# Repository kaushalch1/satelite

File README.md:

# Live ysws satelite

## satelite Telemetry and Mission Control System

**Live-X01** is a miniature CubeSat-inspired flight computer and telemetry system built around an ESP32. The project combines real-time sensor monitoring, telemetry logging, system diagnostics, and a dedicated mission-control interface.

The design is intended to look and behave like a small satellite flight computer while remaining practical to prototype and simulate.

---

## Project Overview

Live satelite monitors the satellite's internal systems and displays important telemetry through an OLED interface.

The system can monitor:

- Temperature
- Acceleration and orientation
- Battery voltage
- Storage status
- System status
- Mission status
- Twitch Live stream status

Telemetry can also be stored on a microSD card for later analysis.

---

## Main Features

### Flight Computer

The ESP32 acts as the main flight computer responsible for:

- Sensor communication
- Telemetry processing
- Display control
- Data logging
- Button input
- Status indication
- Mission-state management

### Telemetry Display

The OLED provides a compact mission dashboard.

Example:

```text
CUBESAT-X01
----------------
HACK CLUB LIVE
STREAM: ONLINE

TEMP: 27.4 C
BAT: 82%
IMU: ONLINE
SD: ONLINE

MISSION: ACTIVE

```
##pcb:

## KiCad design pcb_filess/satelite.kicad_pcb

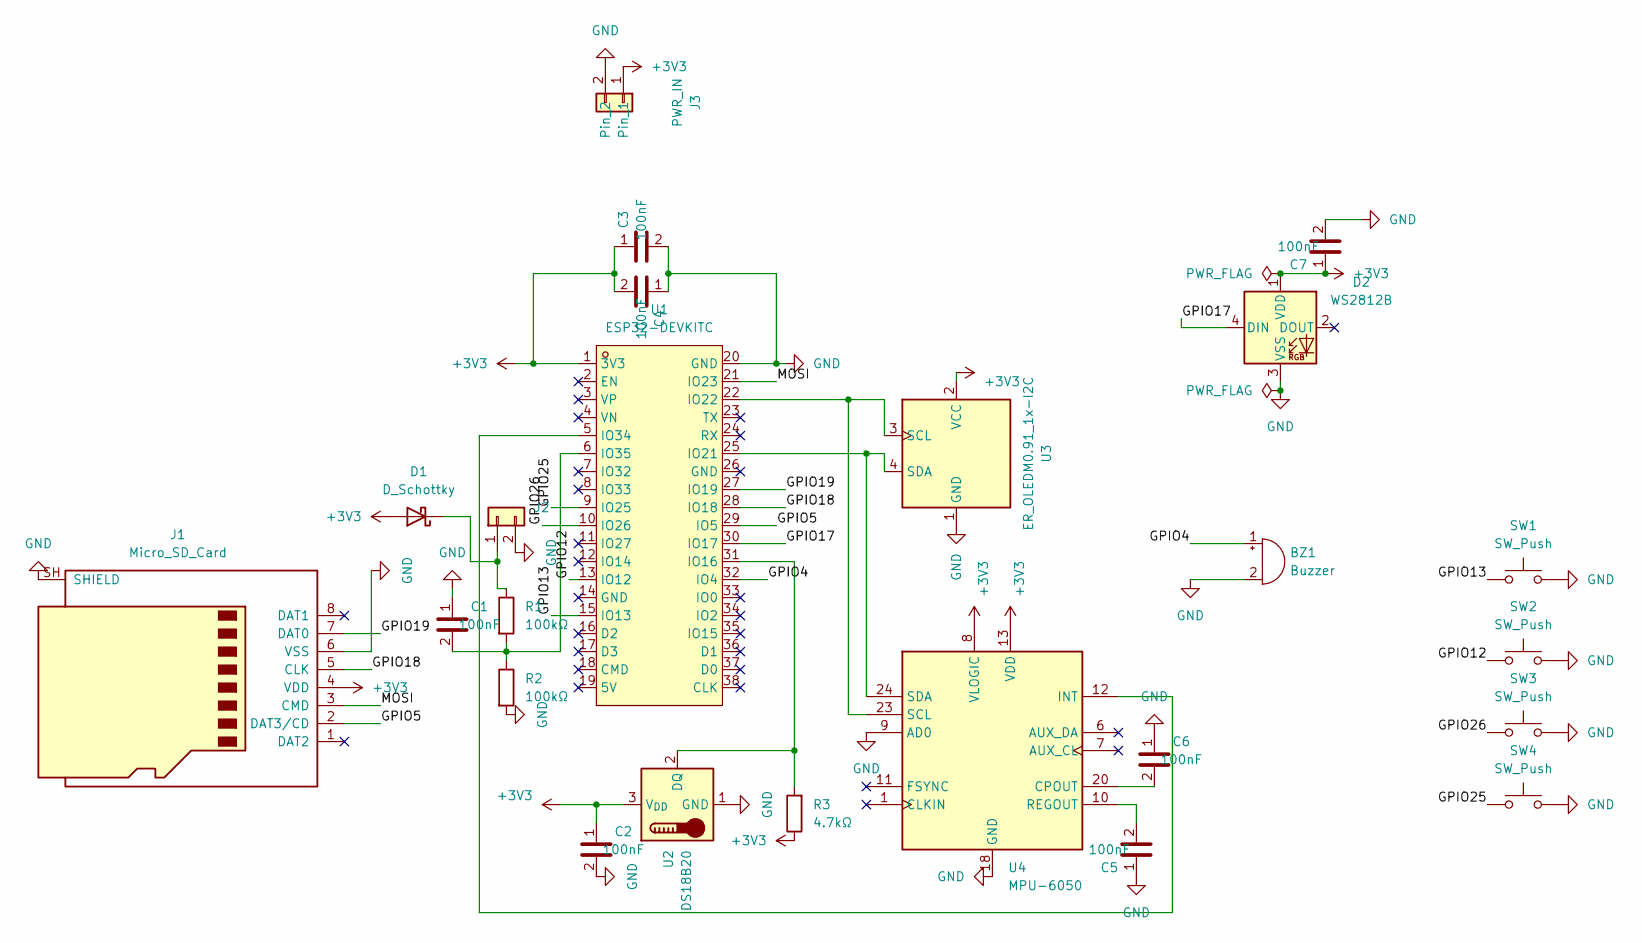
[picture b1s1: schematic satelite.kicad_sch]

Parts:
BZ1: Buzzer; Buzzer_12x9.5RM7.6
C1, C2, C3, C4, C5, C6, C7: 100nF; C_0603_1608Metric
D1: D_Schottky; D_SOD-123
D2: WS2812B; LED_WS2812B_PLCC4_5.0x5.0mm_P3.2mm
J1: Micro_SD_Card; microSD_HC_Molex_104031-0811
J2: Conn_01x02; JST_XH_B2B-XH-A_1x02_P2.50mm_Vertical
J3: PWR_IN; JST_PH_S2B-PH-K_1x02_P2.00mm_Horizontal
R1, R2: 100kΩ; R_0603_1608Metric
R3: 4.7kΩ; R_0603_1608Metric
SW1, SW2, SW3, SW4: SW_Push; SW_SPST_PTS645Sx43SMTR92
U1: ESP32-DEVKITC; BULETM-SMD_ESP32-DEVKITC; MPN ESP32-DevKitC; LCSC Part C571180
U2: DS18B20; TO-92_Inline
U3: ER_OLEDM0.91_1x-I2C
U4: MPU-6050; InvenSense_QFN-24_4x4mm_P0.5mm

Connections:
+3V3: C2.1, C3.1, C4.2, C7.1, D1.2 (A), D2.1 (VDD), J1.4 (VDD), J3.1, R3.1, U1.1 (3V3), U2.3 (V_{DD}), U3.2 (VCC), U4.8 (VLOGIC), U4.13 (VDD)
/GPIO4: BZ1.1 (+), U1.32 (IO4)
/GPIO5: J1.2 (DAT3/CD), U1.29 (IO5)
/GPIO12: SW2.1, U1.13 (IO12)
/GPIO13: SW1.1, U1.15 (IO13)
/GPIO17: D2.4 (DIN), U1.30 (IO17)
/GPIO18: J1.5 (CLK), U1.28 (IO18)
/GPIO19: J1.7 (DAT0), U1.27 (IO19)
/GPIO25: SW4.1, U1.9 (IO25)
/GPIO26: SW3.1, U1.10 (IO26)
/MOSI: J1.3 (CMD), U1.21 (IO23)
GND: BZ1.2 (-), C1.1, C2.2, C3.2, C4.1, C5.1, C6.1, C7.2, D2.3 (VSS), J1.6 (VSS), J1.SH (SHIELD), J2.2, J3.2, R2.2, SW1.2, SW2.2, SW3.2, SW4.2, U1.20 (GND), U2.1 (GND), U3.1 (GND), U4.9 (AD0), U4.18 (GND)
unnamed: D1.1 (K), J2.1, R1.1
unnamed: R3.2, U1.31 (IO16), U2.2 (DQ)
unnamed: U1.25 (IO21), U3.4 (SDA), U4.24 (SDA)
unnamed: U1.22 (IO22), U3.3 (SCL), U4.23 (SCL)
unnamed: U1.5 (IO34), U4.12 (INT)
unnamed: C1.2, R1.2, R2.1, U1.6 (IO35)
unnamed: C6.2, U4.20 (CPOUT)
unnamed: C5.2, U4.10 (REGOUT)

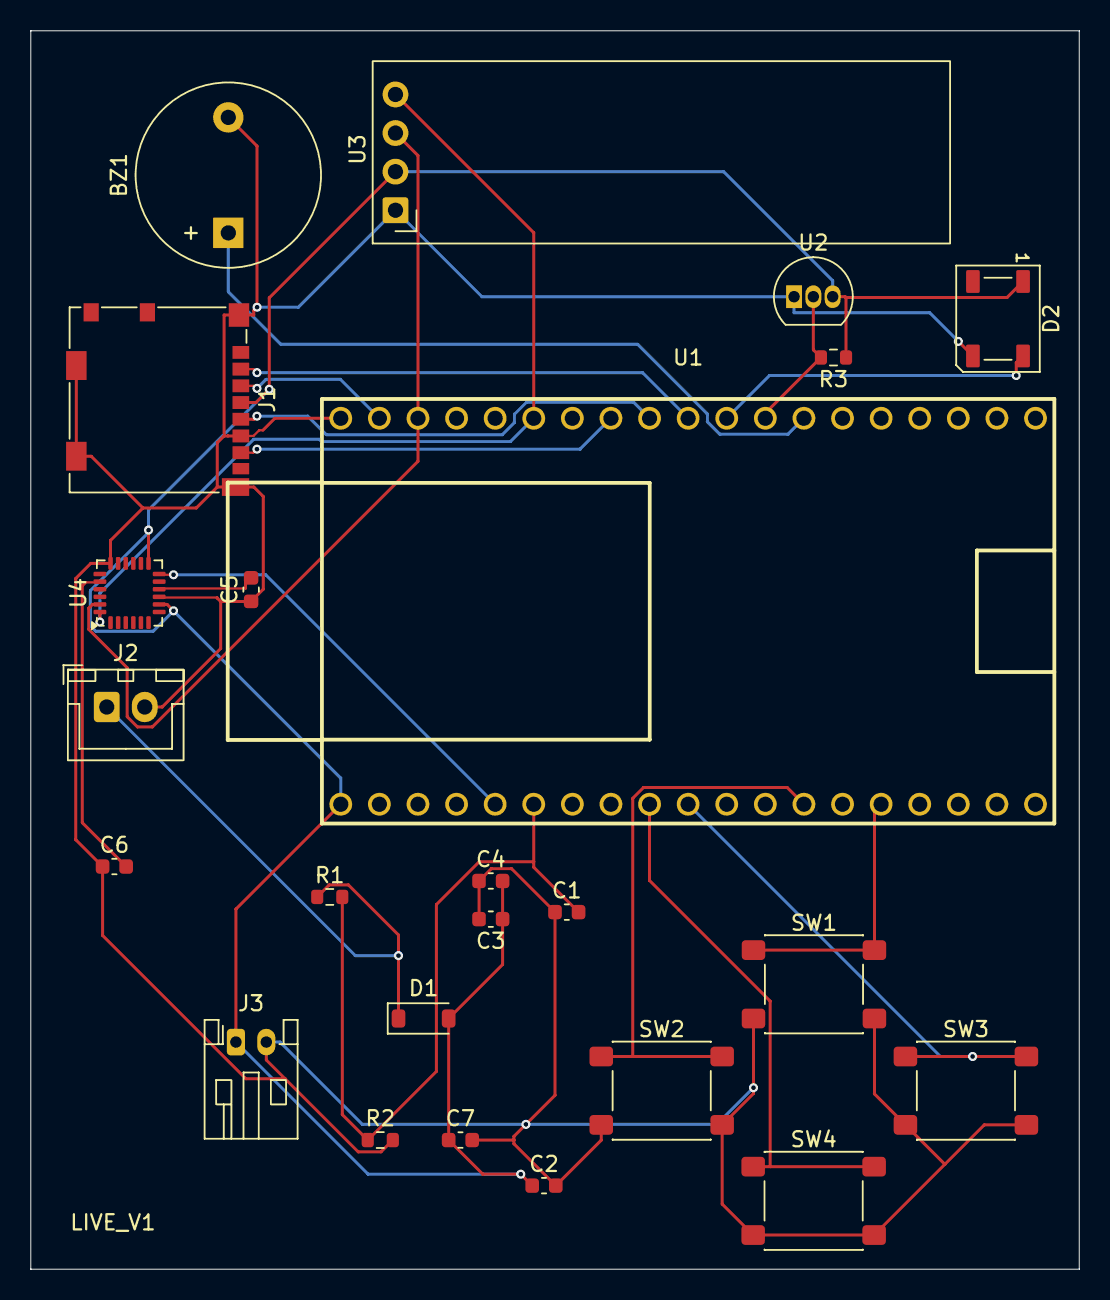
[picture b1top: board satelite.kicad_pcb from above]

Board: 2 copper layers, 69.0 x 81.5 mm, 24 parts (0 on the bottom side), 20 nets.
